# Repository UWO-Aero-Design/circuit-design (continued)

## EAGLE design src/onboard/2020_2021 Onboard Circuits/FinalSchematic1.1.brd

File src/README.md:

# WE Aero Design Onboard Hardware

## Goal
The hardware soloution will contain sensors that allow the team to accurately determine the height and position of the aircraft at any given moment. Also, the system should allow for communication with the ground station through an onboard radio. Logging of in-flight data and accurate GPS information will be necessary. Finally, the system must be able to control 16 individual servos or DC motors.

## Design
Below are screenshots of the current revision of the schematic and board (created in Eagle).
###Schematic

### Board

## Features
#### Radio
[RFM95W](https://www.adafruit.com/product/3072)

#### IMU
[MPU9250](https://www.sparkfun.com/products/13762)

#### Evironment Sensing
[MPL3115A2](https://www.adafruit.com/product/1893)

#### GPS
[Adafruit Ultimate GPS Breakout](https://www.adafruit.com/product/746?gclid=CjwKCAjwscDpBRBnEiwAnQ0HQNEhq5xu14W7TX12W0gVZqHBnbDJNApMf9mEeb73NOOZy2kR0mpCVRoCgI8QAvD_BwE)

#### Battery Monitoring
[INA219](https://www.adafruit.com/product/904)

#### Servo Driver
[PCA9686](https://cdn-shop.adafruit.com/datasheets/PCA9685.pdf)

#### Power
[L7805 and L7806](https://www.mouser.ca/datasheet/2/389/l78m-974157.pdf)

## TODO
- [x] Select parts
- [x] Create schematic
- [x] Layout board
- [ ] Route board
- [ ] Add Aero Design logo to board
- [ ] Order board
- [ ] Test board

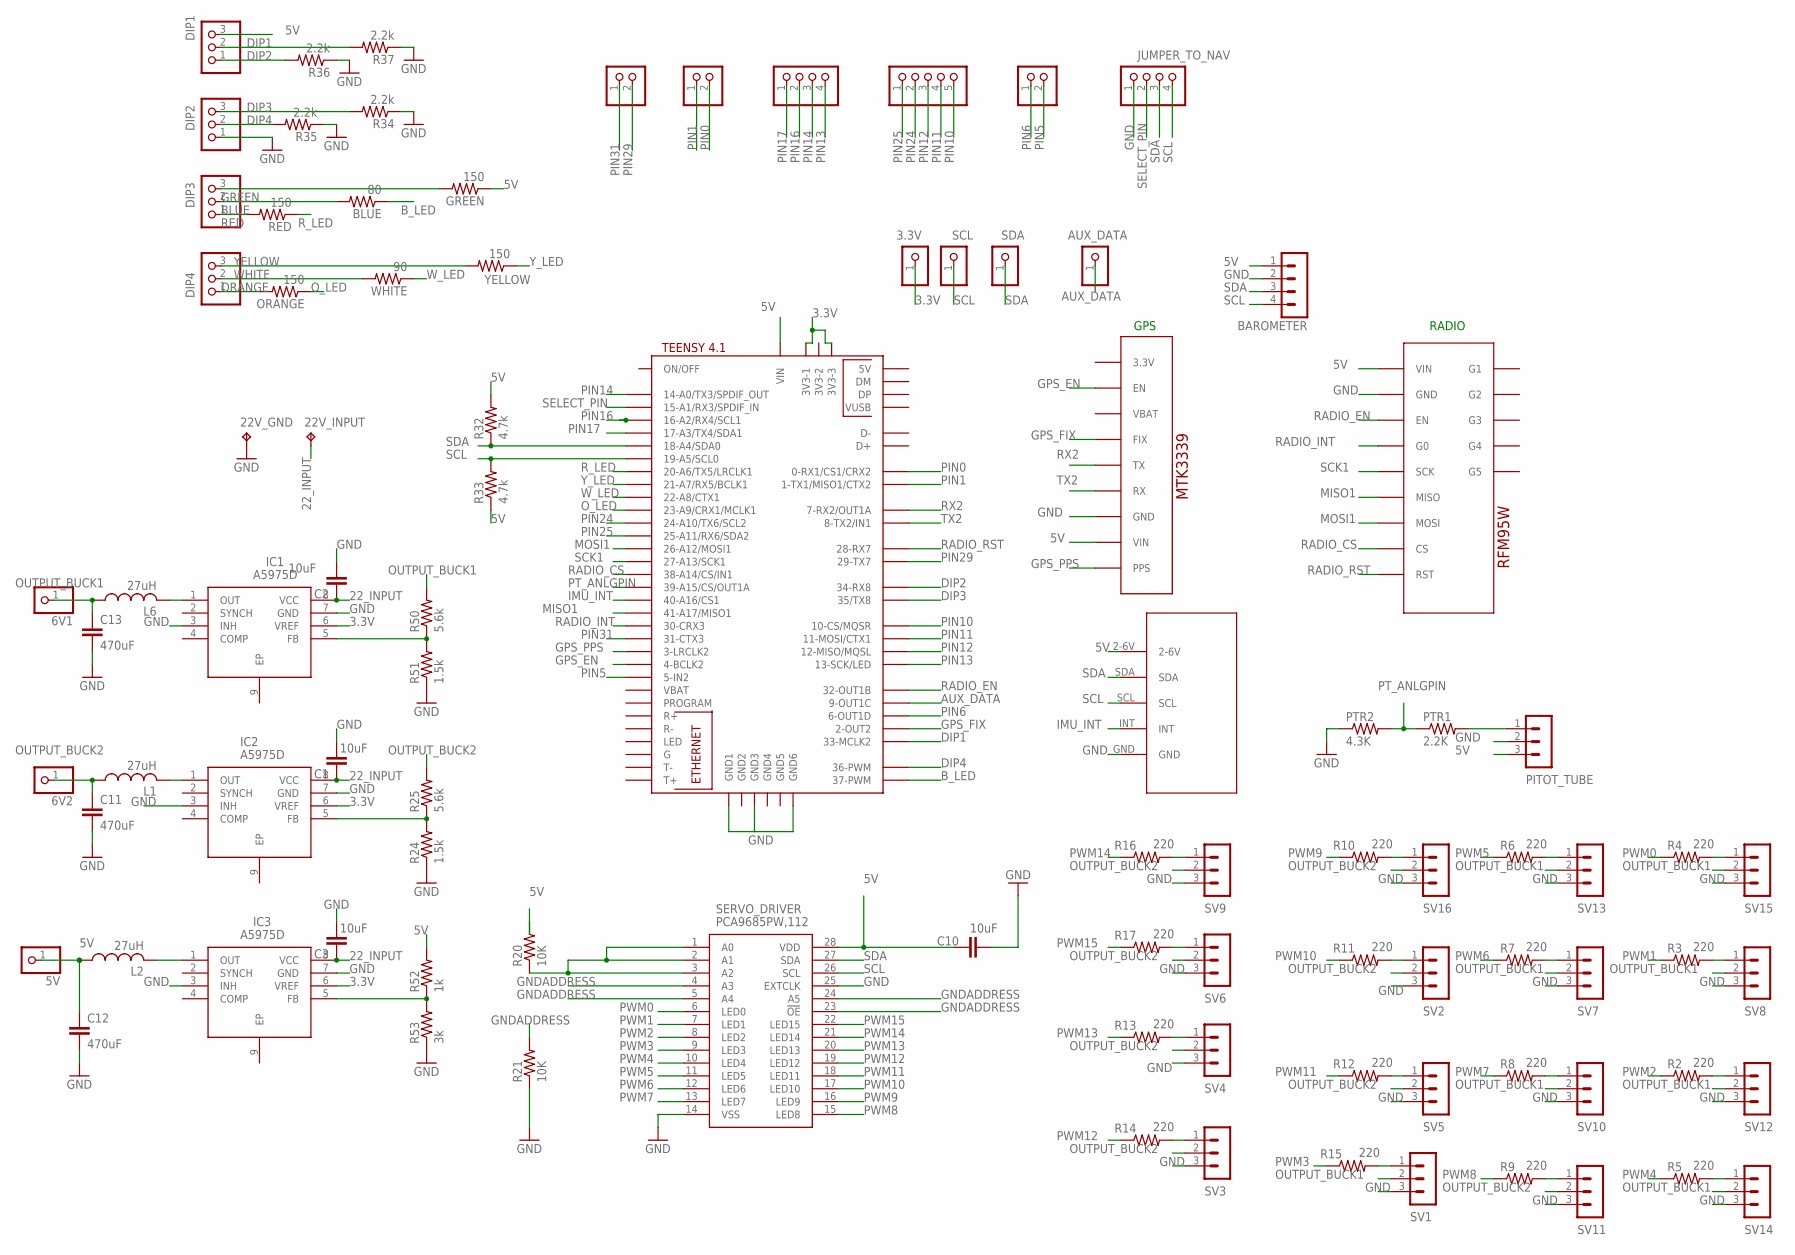
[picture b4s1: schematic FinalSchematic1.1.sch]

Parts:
1, 2, 5: PINHD-1X2; 1X02
3: PINHD-1X4; 1X04
3.3V, 5V, 6V1, 6V2: PINHD-1X1; 1X01
4: PINHD-1X5; 1X05
22V_GND, 22V_INPUT: TPPAD1-17Y; P1-17Y
AUX_DATA: PINHD-1X1; 1X01
BAROMETER: MA04-1
BLUE: 80; 0204/7
C1, C2, C3, C10: 10uF; C2.5-3
C11, C12, C13: 470uF; C2.5-3
DIP1, DIP2, DIP3, DIP4: PINHD-1X3; 1X03
GPSMTK3339: ADAFRUIT_MTK3339_GPS
GREEN: 150; 0204/7
IC1, IC2, IC3: A5975D; SOIC127P600X170-9N
IMU: ICM20948BREAKOUTDEVICE; ICM20948BREAKOUT
JUMPER_TO_NAV: PINHD-1X4; 1X04
L1, L2, L6: 27uH; TFI0307
ORANGE: 150; 0204/7
PITOT_TUBE: MA03-1
PTR1: 2.2K; 0204/7
PTR2: 4.3K; 0204/7
R2, R3, R4, R5, R6, R7, R8, R9, R10, R11, R12, R13, R14, R15, R16, R17: 220; 0204/7
R20, R21: 10K; 0204/7
R24, R51: 1.5k; 0204/7
R25, R50: 5.6k; 0204/7
R32, R33: 4.7k; 0204/7
R34, R35, R36, R37: 2.2k; 0204/7
R52: 1k; 0204/7
R53: 3k; 0204/7
RADIO: ADAFRUIT_RFM95W_LORA_RADIO
RED: 150; 0204/7
SCL: PINHD-1X1; 1X01
SDA: PINHD-1X1; 1X01
SERVO_DRIVER: PCA9685PW,112; SOP65P640X110-28N
SV1, SV2, SV3, SV4, SV5, SV6, SV7, SV8, SV9, SV10, SV11, SV12, SV13, SV14, SV15, SV16: MA03-1
TEENSY4.1: TEENSY41
WHITE: 90; 0204/7
YELLOW: 150; 0204/7

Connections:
3.3V: 3.3V.1, IC1.6 (VREF), IC2.6 (VREF), IC3.6 (VREF), TEENSY4.1.3V3-1, TEENSY4.1.3V3-3
5V: 5V.1, BAROMETER.1, C10.1, C12.1, DIP1.3, GPSMTK3339.VIN, GREEN.1, IMU.2-6V, L2.1, PITOT_TUBE.3, R20.2, R32.2, R33.1, R52.2, RADIO.1 (VIN), SERVO_DRIVER.28 (VDD), TEENSY4.1.VIN
22_INPUT: 22V_INPUT.TP, C1.1, C2.1, C3.1, IC1.8 (VCC), IC2.8 (VCC), IC3.8 (VCC)
AUX_DATA: AUX_DATA.1, TEENSY4.1.9-OUT1C
BLUE: BLUE.2, DIP3.2
B_LED: BLUE.1, TEENSY4.1.37-PWM
DIP1: DIP1.2, R37.2, TEENSY4.1.33-MCLK2
DIP2: DIP1.1, R36.2, TEENSY4.1.34-RX8
DIP3: DIP2.3, R34.2, TEENSY4.1.35-TX8 (35/TX8)
DIP4: DIP2.2, R35.2, TEENSY4.1.36-PWM
GND: 22V_GND.TP, BAROMETER.2, C1.2, C2.2, C3.2, C10.2, C11.2, C12.2, C13.2, DIP2.1, GPSMTK3339.GND, IC1.3 (INH), IC1.7 (GND), IC2.3 (INH), IC2.7 (GND), IC3.3 (INH), IC3.7 (GND), IMU.GND, JUMPER_TO_NAV.1, PITOT_TUBE.2, PTR2.1, R21.1, R24.1, R34.1, R35.1, R36.1, R37.1, R51.1, R53.1, RADIO.2 (GND), SERVO_DRIVER.14 (VSS), SERVO_DRIVER.25 (EXTCLK), SV1.3, SV2.3, SV3.3, SV4.3, SV5.3, SV6.3, SV7.3, SV8.3, SV9.3, SV10.3, SV11.3, SV12.3, SV13.3, SV14.3, SV15.3, SV16.3, TEENSY4.1.GND1, TEENSY4.1.GND3, TEENSY4.1.GND6
GNDADDRESS: R21.2, SERVO_DRIVER.4 (A3), SERVO_DRIVER.5 (A4), SERVO_DRIVER.23 (!OE), SERVO_DRIVER.24 (A5)
GPS_EN: GPSMTK3339.EN, TEENSY4.1.4-BCLK2
GPS_FIX: GPSMTK3339.FIX, TEENSY4.1.2-OUT2
GPS_PPS: GPSMTK3339.PPS, TEENSY4.1.3-LRCLK2
GREEN: DIP3.3, GREEN.2
IMU_INT: IMU.INT, TEENSY4.1.40-A16/CS1
MISO1: RADIO.6 (MISO), TEENSY4.1.41-A17/MISO1
MOSI1: RADIO.7 (MOSI), TEENSY4.1.26-A12/MOSI1
unnamed: R14.2, SV3.1
unnamed: PITOT_TUBE.1, PTR1.2
unnamed: IC3.1 (OUT), L2.2
unnamed: IC1.1 (OUT), L6.2
unnamed: IC1.5 (FB), R50.1, R51.2
unnamed: IC2.1 (OUT), L1.2
unnamed: IC3.5 (FB), R52.1, R53.2
unnamed: IC2.5 (FB), R24.2, R25.1
unnamed: R10.2, SV16.1
unnamed: R20.1, SERVO_DRIVER.1 (A0), SERVO_DRIVER.2 (A1), SERVO_DRIVER.3 (A2)
unnamed: R6.2, SV13.1
unnamed: R4.2, SV15.1
unnamed: R3.2, SV8.1
unnamed: R7.2, SV7.1
unnamed: R11.2, SV2.1
unnamed: R15.2, SV1.1
unnamed: R2.2, SV12.1
unnamed: R5.2, SV14.1
unnamed: R9.2, SV11.1
unnamed: R8.2, SV10.1
unnamed: R12.2, SV5.1
unnamed: R16.2, SV9.1
unnamed: R17.2, SV6.1
unnamed: R13.2, SV4.1
ORANGE: DIP4.1, ORANGE.2
OUTPUT_BUCK1: 6V1.1, C13.1, L6.1, R50.2, SV1.2, SV7.2, SV8.2, SV10.2, SV12.2, SV13.2, SV14.2, SV15.2
OUTPUT_BUCK2: 6V2.1, C11.1, L1.1, R25.2, SV2.2, SV3.2, SV4.2, SV5.2, SV6.2, SV9.2, SV11.2, SV16.2
O_LED: ORANGE.1, TEENSY4.1.23-A9/CRX1/MCLK1
PIN0: 2.2, TEENSY4.1.0-RX1/CS1/CRX2
PIN1: 2.1, TEENSY4.1.1-TX1/MISO1/CTX2
PIN5: 5.2, TEENSY4.1.5-IN2
PIN6: 5.1, TEENSY4.1.6-OUT1D
PIN10: 4.5, TEENSY4.1.10-CS\MQSR (10-CS/MQSR)
PIN11: 4.4, TEENSY4.1.11-MOSI/CTX1
PIN12: 4.3, TEENSY4.1.12-MISO/MQSL
PIN13: 3.4, TEENSY4.1.13-SCK/LED
PIN14: 3.3, TEENSY4.1.14-A0/TX3/SPDIF_OUT
PIN16: 3.2, TEENSY4.1.16-A2/RX4/SCL1
PIN17: 3.1, TEENSY4.1.17-A3/TX4/SDA1
PIN24: 4.2, TEENSY4.1.24-A10/TX6/SCL2
PIN25: 4.1, TEENSY4.1.25-A11/RX6/SDA2
PIN29: 1.2, TEENSY4.1.29-TX7
PIN31: 1.1, TEENSY4.1.31-CTX3
PT_ANLGPIN: PTR1.1, PTR2.2, TEENSY4.1.39-A15/CS/OUT1A
PWM0: R4.1, SERVO_DRIVER.6 (LED0)
PWM1: R3.1, SERVO_DRIVER.7 (LED1)
PWM2: R2.1, SERVO_DRIVER.8 (LED2)
PWM3: R15.1, SERVO_DRIVER.9 (LED3)
PWM4: R5.1, SERVO_DRIVER.10 (LED4)
PWM5: R6.1, SERVO_DRIVER.11 (LED5)
PWM6: R7.1, SERVO_DRIVER.12 (LED6)
PWM7: R8.1, SERVO_DRIVER.13 (LED7)
PWM8: R9.1, SERVO_DRIVER.15 (LED8)
PWM9: R10.1, SERVO_DRIVER.16 (LED9)
PWM10: R11.1, SERVO_DRIVER.17 (LED10)
PWM11: R12.1, SERVO_DRIVER.18 (LED11)
PWM12: R14.1, SERVO_DRIVER.19 (LED12)
PWM13: R13.1, SERVO_DRIVER.20 (LED13)
PWM14: R16.1, SERVO_DRIVER.21 (LED14)
PWM15: R17.1, SERVO_DRIVER.22 (LED15)
RADIO_CS: RADIO.8 (CS), TEENSY4.1.38-A14/CS/IN1
RADIO_EN: RADIO.3 (EN), TEENSY4.1.32-OUT1B
RADIO_INT: RADIO.4 (G0), TEENSY4.1.30-CRX3
RADIO_RST: RADIO.9 (RST), TEENSY4.1.28-RX7
RED: DIP3.1, RED.2
RX2: GPSMTK3339.TX, TEENSY4.1.7-RX2/OUT1A
R_LED: RED.1, TEENSY4.1.20-A6/TX5/LRCLK1
SCK1: RADIO.5 (SCK), TEENSY4.1.27-A13/SCK1
SCL: BAROMETER.4, IMU.SCL, JUMPER_TO_NAV.4, R33.2, SCL.1, SERVO_DRIVER.26 (SCL), TEENSY4.1.19-A5/SCL0
SDA: BAROMETER.3, IMU.SDA, JUMPER_TO_NAV.3, R32.1, SDA.1, SERVO_DRIVER.27 (SDA), TEENSY4.1.18-A4/SDA0
SELECT_PIN: JUMPER_TO_NAV.2, TEENSY4.1.15-A1/RX3/SPDIF_IN
TX2: GPSMTK3339.RX, TEENSY4.1.8-TX2/IN1
WHITE: DIP4.2, WHITE.2
W_LED: TEENSY4.1.22-A8/CTX1, WHITE.1
YELLOW: DIP4.3, YELLOW.2
Y_LED: TEENSY4.1.21-A7/RX5/BCLK1, YELLOW.1

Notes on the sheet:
RADIO
GPS

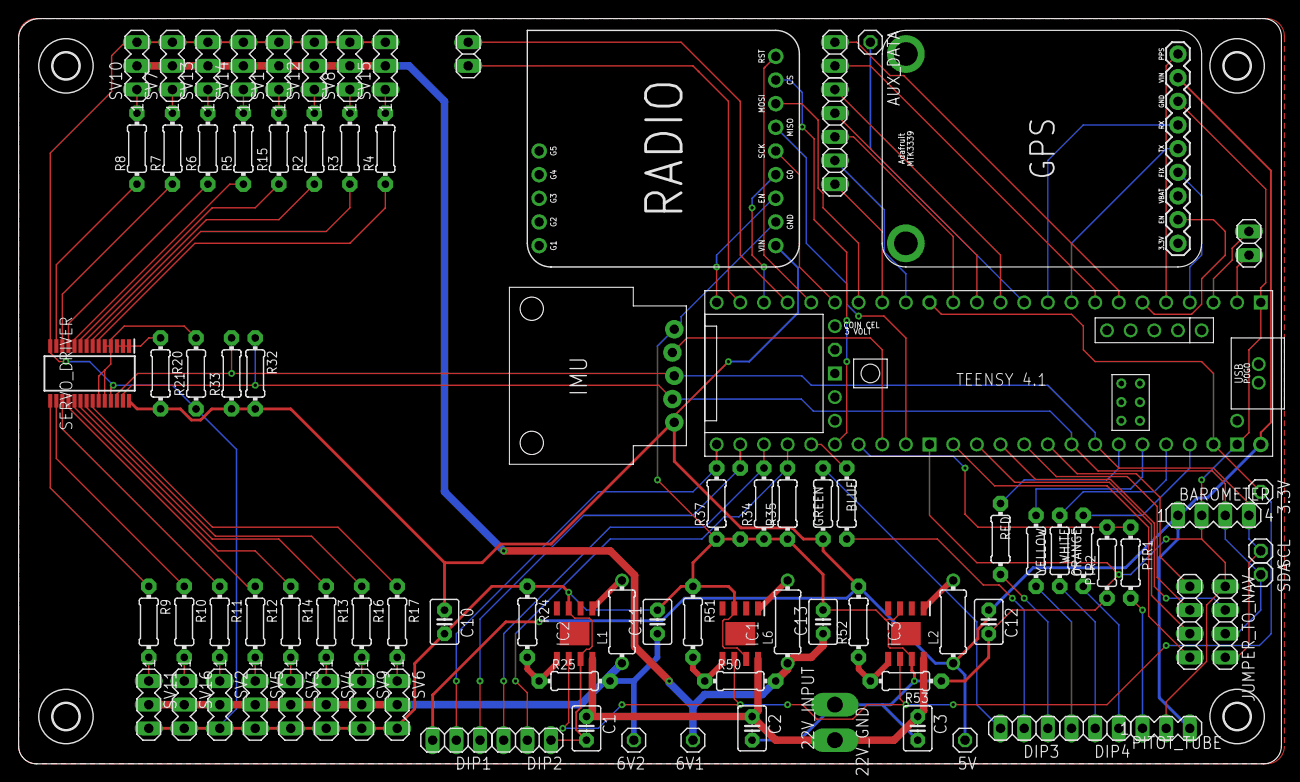
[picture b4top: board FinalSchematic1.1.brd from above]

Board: 2 copper layers, 135.6 x 80.0 mm, 97 parts (1 on the bottom side), 95 nets.

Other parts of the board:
U$1, U$3, U$4, U$5: 2,8

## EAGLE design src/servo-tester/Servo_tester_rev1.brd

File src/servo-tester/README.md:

# WE Aero Design Servo Tester Hardware

## Goal
To have an easy and portable way to find the bounds of the servos used to actuate the drop mechanism.

## Design
Below are screenshots of the current revision of the schematic and board (created in Eagle).

### Schematic

### Board

## Features
0.96" High contrast OLED display  
Battery monitor circuit  
Easily replaceable 9v battery, expected 2-4 hour life

## TODO
- [x] Create schematic
- [ ] Solder board
- [ ] Write code
- [ ] Build case

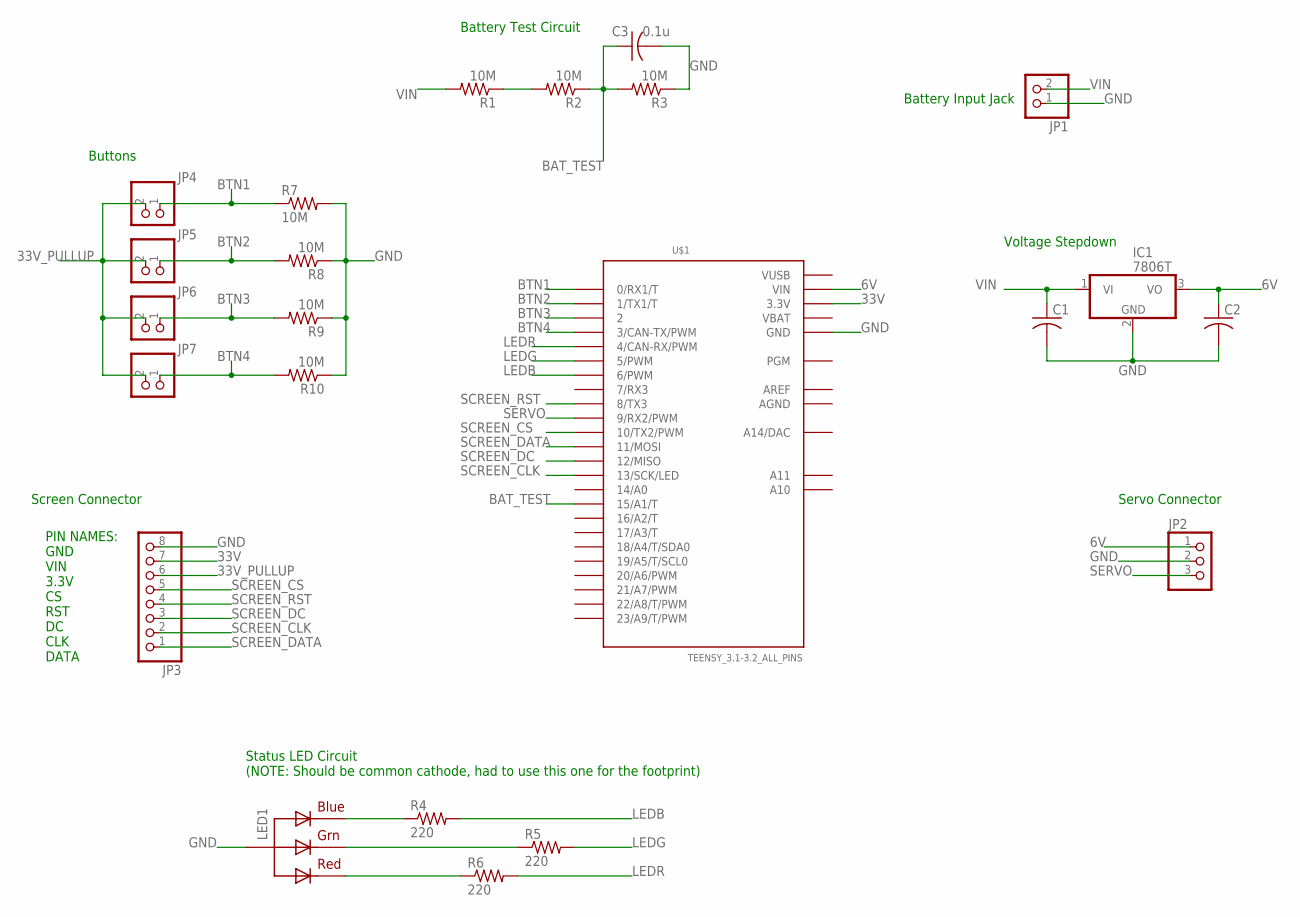
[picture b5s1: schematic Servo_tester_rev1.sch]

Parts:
C1, C2: C-US050-024X044; C050-024X044
C3: 0.1u; C050-024X044
IC1: 7806T; TO220H
JP1, JP4, JP5, JP6, JP7: HEADER-1X2ROUND; 1X02_ROUND
JP2: HEADER-1X3ROUND; 1X03_ROUND
JP3: HEADER-1X870MIL; 1X08_ROUND_70
LED1: RGBLED_CA-5MM; LED5MMRGB
R1, R2, R3, R7, R8, R9, R10: 10M; 0204/5
R4, R5, R6: 220; 0204/5
U$1: TEENSY_3.1-3.2_ALL_PINS; TEENSY_3.0-3.2&LC_ALL_PINS

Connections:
6V: C2.1, IC1.3 (VO), JP2.1, U$1.VIN
33V: JP3.7, U$1.3.3V, U$1.3.3V1 (3.3V)
33V_PULLUP: JP3.6, JP4.2, JP5.2, JP6.2, JP7.2
AGND: U$1.AGND
AREF: U$1.AREF
BAT_TEST: C3.1, R2.1, R3.2, U$1.15/A1 (15/A1/T)
BTN1: JP4.1, R7.1, U$1.0 (0/RX1/T)
BTN2: JP5.1, R8.2, U$1.1 (1/TX1/T)
BTN3: JP6.1, R9.2, U$1.2
BTN4: JP7.1, R10.2, U$1.3 (3/CAN-TX/PWM)
GND: C1.2, C2.2, C3.2, IC1.2 (GND), JP1.1, JP2.2, JP3.8, LED1.2 (VCC), R3.1, R7.2, R8.1, R9.1, R10.1, U$1.GND, U$1.GND1 (GND)
LEDB: R4.2, U$1.6 (6/PWM)
LEDG: R5.2, U$1.5 (5/PWM)
LEDR: R6.2, U$1.4 (4/CAN-RX/PWM)
unnamed: LED1.1 (RED), R6.1
unnamed: LED1.4 (BLUE), R4.1
unnamed: LED1.3 (GREEN), R5.1
unnamed: R1.1, R2.2
SCREEN_CLK: JP3.2, U$1.13 (13/SCK/LED)
SCREEN_CS: JP3.5, U$1.10 (10/TX2/PWM)
SCREEN_DATA: JP3.1, U$1.11 (11/MOSI)
SCREEN_DC: JP3.3, U$1.12 (12/MISO)
SCREEN_RST: JP3.4, U$1.8 (8/TX3)
SERVO: JP2.3, U$1.9 (9/RX2/PWM)
VBAT: U$1.VBAT
VIN: C1.1, IC1.1 (VI), JP1.2, R1.2
VUSB: U$1.VUSB

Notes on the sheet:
PIN NAMES: GND VIN 3.3V CS RST DC CLK DATA
Battery Input Jack
Battery Test Circuit
Voltage Stepdown
Servo Connector
Status LED Circuit (NOTE: Should be common cathode, had to use this one for the footprint)
Screen Connector
Buttons

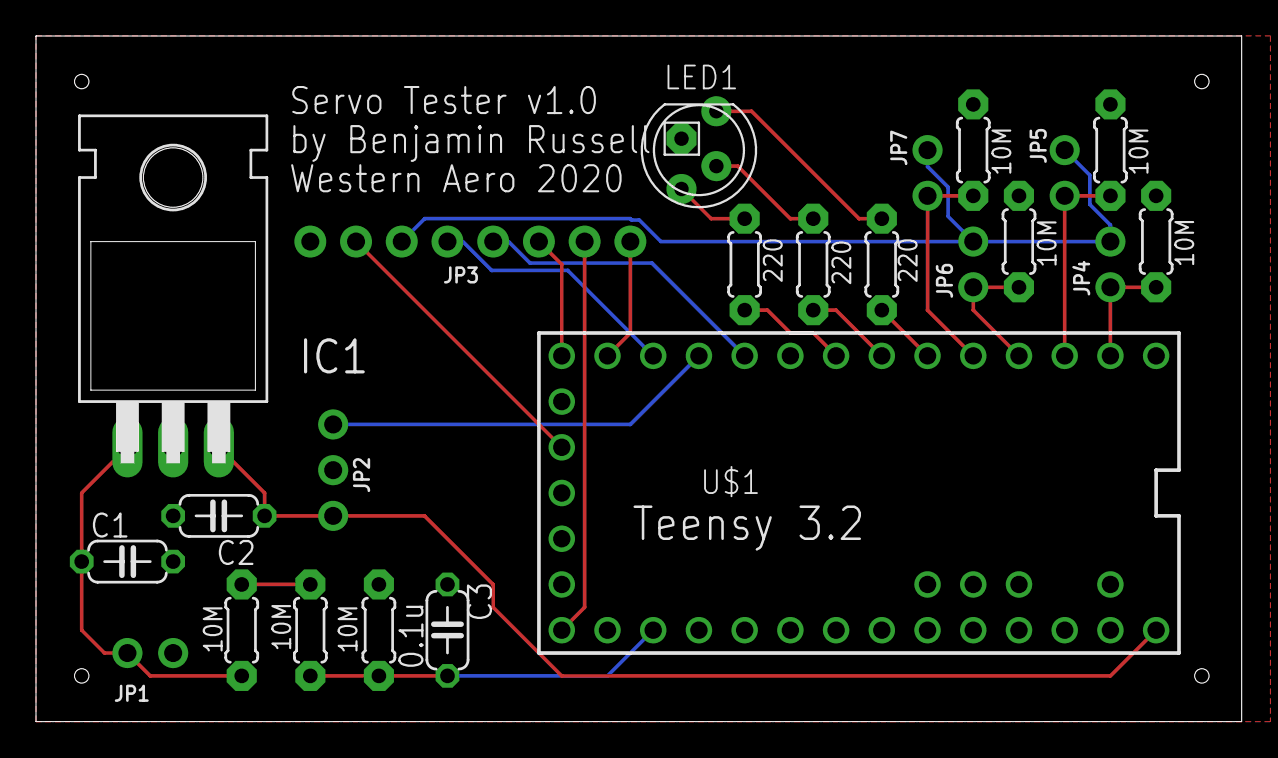
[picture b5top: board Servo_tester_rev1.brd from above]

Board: 2 copper layers, 67.0 x 38.1 mm, 23 parts (0 on the bottom side), 23 nets.

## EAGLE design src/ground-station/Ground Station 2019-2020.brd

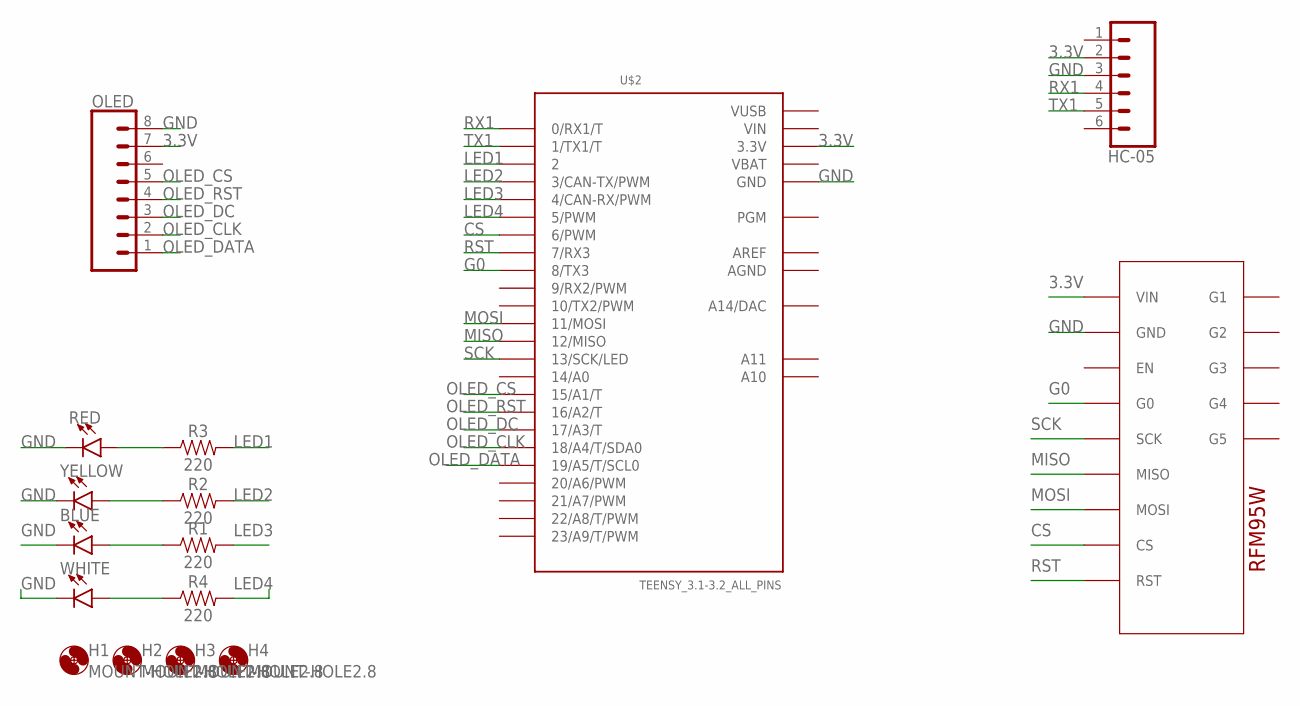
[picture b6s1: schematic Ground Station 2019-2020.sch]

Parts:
BLUE: LED5MM; LED_5MM
H1, H2, H3, H4: MOUNT-HOLE2.8; 2,8
HC-05: CONN_06SILK_FEMALE_PTH; 1X06
OLED: CONN_08"; 1X08
R1, R2, R3, R4: 220; AXIAL-0.3
RED: LED5MM; LED_5MM
U1: ADAFRUIT_RFM95W_LORA_RADIO
U$2: TEENSY_3.1-3.2_ALL_PINS; TEENSY_3.0-3.2&LC_ALL_PINS
WHITE: LED5MM; LED_5MM
YELLOW: LED5MM; LED_5MM

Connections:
3.3V: HC-05.2, OLED.7, U1.1 (VIN), U$2.3.3V, U$2.3.3V1 (3.3V)
AGND: U$2.AGND
AREF: U$2.AREF
CS: U1.8 (CS), U$2.6 (6/PWM)
G0: U1.4 (G0), U$2.8 (8/TX3)
GND: BLUE.K (C), HC-05.3, OLED.8, RED.K (C), U1.2 (GND), U$2.GND, U$2.GND1 (GND), WHITE.K (C), YELLOW.K (C)
LED1: R3.P$2 (2), U$2.2
LED2: R2.P$2 (2), U$2.3 (3/CAN-TX/PWM)
LED3: R1.P$2 (2), U$2.4 (4/CAN-RX/PWM)
LED4: R4.P$2 (2), U$2.5 (5/PWM)
MISO: U1.6 (MISO), U$2.12 (12/MISO)
MOSI: U1.7 (MOSI), U$2.11 (11/MOSI)
unnamed: BLUE.A, R1.P$1 (1)
unnamed: R2.P$1 (1), YELLOW.A
unnamed: R3.P$1 (1), RED.A
unnamed: R4.P$1 (1), WHITE.A
OLED_CLK: OLED.2, U$2.18/A4 (18/A4/T/SDA0)
OLED_CS: OLED.5, U$2.15/A1 (15/A1/T)
OLED_DATA: OLED.1, U$2.19/A5 (19/A5/T/SCL0)
OLED_DC: OLED.3, U$2.17/A3 (17/A3/T)
OLED_RST: OLED.4, U$2.16/A2 (16/A2/T)
RST: U1.9 (RST), U$2.7 (7/RX3)
RX1: HC-05.4, U$2.0 (0/RX1/T)
SCK: U1.5 (SCK), U$2.13 (13/SCK/LED)
TX1: HC-05.5, U$2.1 (1/TX1/T)
VBAT: U$2.VBAT
VIN: U$2.VIN
VUSB: U$2.VUSB

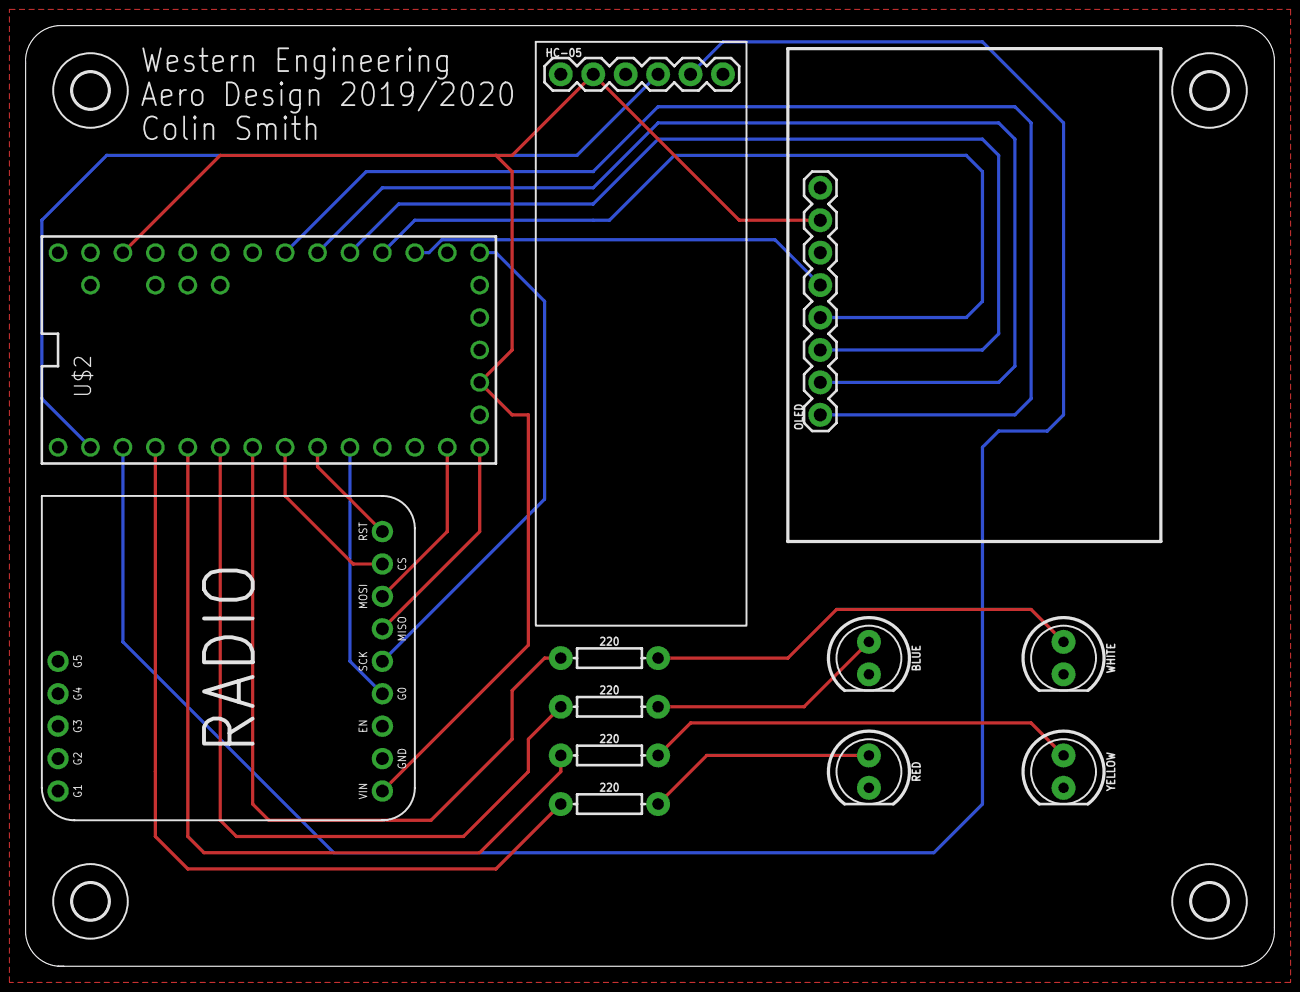
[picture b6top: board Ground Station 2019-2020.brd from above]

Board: 2 copper layers, 97.8 x 73.7 mm, 16 parts (0 on the bottom side), 23 nets.

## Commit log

2019-07-11 First Draft. All components on schematic and board. No routing completed.
2019-07-18 Rewired radio
2019-07-18 Reconfigured components, hid resistors and cut space
2019-07-18 Added reference images
2019-07-18 Added ReadMe
2019-07-18 Moved reference images
2019-07-18 Updated ReadMe again :(
2019-07-25 Added screwholes, adjusted addresses, few other tweaks
2019-08-02 new layout
2019-08-18 Add new voltage regulator
2019-08-23 Changed test point parts. Updated parts list. Adjusted board layout.
2019-09-18 Finished new route.
2019-09-19 no message
2019-09-19 14% reduction
2019-09-24 Finished re-route
2019-10-01 Trace adjustments
2019-10-01 Update text location
2019-10-01 Update part list
2019-10-03 Added manufacturing files
2019-10-09 Trace rework
2019-10-17 Remove battery monitor
2019-10-17 UBEC now supplies 6v with a 5v reg for onboard systems
2019-10-17 Reduce board size
2019-10-17 Update parts list
2019-10-17 Update mounting hole placement
2019-10-19 Generate manufacturing files
2019-10-30 Added groundstation board and schematic files into separate folder. Also placed onboard circuit files in its own folder.
2019-11-21 Schematic and first routing attempt completed.
2019-11-28 Rounded board corners
2020-01-05 Added LCD to board and increased space to accomidate
2020-01-06 pushing servo tester board
    having sourcetree issues, uploaded through webpage
2020-01-09 Added additional LCD, mounting holes and slik screen.
2020-01-09 Fixed some connections and upgraded to ver 2.0
2020-01-09 Added pulldown resistors, mounting holes, and text
2020-01-09 Added larger mounting holes and cleaned up silk screen
2020-01-09 Updated manufacturing files
2020-01-09 Fixed discrepancy between brd and sch, corrected pulldowns
2020-01-09 Changed LCD to OLED display, changed mounting holes.
2020-01-09 fixed DRCs and made smaller
    also added copper fill
2020-01-09 fixed silkscreen
2020-01-09 Added CAM Outputs
2020-01-10 Reorganized
2020-01-20 Release v2.0
2020-01-21 Moved led to unblock usb port, tidied up buttons
2020-01-23 Reformatted
2020-01-23 Add parts list
2020-01-23 Update part order
2020-01-23 Updated servo tester screenshots
2021-02-03 Reorganized 2019 and 2020 files into its own folder. Adding 2020/2021 board schematic and board layout of both main Teensy and navigation Teensy.
2021-02-03 Adding pictures of the schematics and boards of the nav and main teensy.
2021-02-04 Created bigger board
2021-02-20 Removed old board and schematic. Replaced with the new and larger board and schematic. Also updated the photos of both.
2021-02-20 Removing the old schematic and board. (1.0 files)
2021-02-20 Rounded corners of navigation board. Made corner radius same on both boards.
2021-02-24 Updated board using the jlcpcb2layer.dru file for DRC check. Added names next to pinheaders. Adjusted silkscreen of component names. Updated photos of baord and schematic.
2021-02-24 Changed Pinheader side names to Tplace on both boards
2021-02-24 Updated photos of both boards.
2021-02-25 Removed 5V lines as one layer is a 5V pour so they were not needed because the components are through hole. Then updated photos of both boards
2021-02-25 Submitting proper photo of Nav Board.
2021-02-26 Changed hole sizes for both board to 3mm for M3 screws and made boards slilghtly larger to have room around the holes without disrupting the wire traces. Updated photos of both boards.
2021-02-26 Removed leftover wire trace on main board.
2021-03-08 Made a list of components used in each board as well as a list of price and where we got the components from.
2022-02-07 Added button connection, rewired radio, removed pitot tube, split into pages
2022-02-08 Added 5v connector
2022-02-09 Added button wires and fixed 5v input
2022-02-09 Added 6v->5v LDO regulator
2022-02-09 Added pulldown on select pin and added wiring for aux pin
2022-02-09 Formatting changes and 6v test point
2022-02-09 Added bulk decoupling
2022-02-13 Added BMP280 I2C Part
    Added to SCH sheet 4
2022-02-13 Switched 6v LDO to MIC29310-5.0BT
2022-02-13 Removed old schematic, moved current schematic up a level
2022-02-13 Removed old baro
2022-02-14 Rewired pins for easier routing
2022-02-22 Added BMP 280 library component
2022-02-22 Added new BMP280 component to onboard
2022-02-23 First routing attempt Still need to fix silkscreen
2022-02-23 Added 3.3 solderpad
2022-02-23 Renamed main board files
2022-02-23 Exported 1.3 ref pdf
2022-02-27 Added gnd test point
2022-03-01 Performed ERC and made changes
2022-03-01 Updated BMP 280 VIN pin to be IO
2022-03-01 Moved power supply silkscreen for visibility
2022-03-02 Approved ERC warnings for header connections
2022-03-02 Modified silkscreen and generated Gerbers
2022-03-07 Rounded PCB edges
2022-03-27 final preperations for onboard PCB ordering
2023-01-07 Update for TBS Unify FPV transmitter
2023-01-07 AKK iteration (incomplete)
2023-08-25 john's gnd station board design added
2023-08-25 added alex's gnd station board
2023-09-01 removed 3.3v regulator, spaced out wires
2023-12-02 first iteration of order board
2024-01-18 added 2022/2023 PA board and changes to current gnd station board
